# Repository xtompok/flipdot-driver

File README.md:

# flipdot-driver
Driver for flipdot displays

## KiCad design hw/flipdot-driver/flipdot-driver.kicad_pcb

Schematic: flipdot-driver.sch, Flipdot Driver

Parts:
C2: 47u; CP_Radial_D6.3mm_P2.50mm
C5, C6, C7, C8, C17, C22: 100n; C_0603_1608Metric
C9: 10u; C_0805_2012Metric
C10: 10n; C_0603_1608Metric
C11: 22u; C_0805_2012Metric
C12, C13: 10p; C_0603_1608Metric
C14, C15: 27p; C_0603_1608Metric
C16, C21, C23: 680u; CP_Radial_D10.0mm_P5.00mm
C18, C19: 470n; C_0603_1608Metric
C20: 1u; C_0603_1608Metric
D2: SK34; D_SMC
D6: SK33; D_SMC
D7, D8: LED; LED_D3.0mm
F1: 200mA; Fuse_1206_3216Metric
F2: Polyfuse; Fuse_1812_4532Metric
FID1, FID2, FID3: Fiducial; Fiducial_0.75mm_Dia_1.5mm_Outer
H1, H2: MountingHole_Pad; MountingHole_3.2mm_M3_DIN965_Pad
J1: DISPLAY; IDC-Header_2x10_P2.54mm_Vertical
J2: NRF_CON; PinSocket_2x04_P2.54mm_Vertical
J3: Prog; Molex_KK-254_AE-6410-05A_1x05_P2.54mm_Vertical
J4: I2C; Molex_KK-254_AE-6410-04A_1x04_P2.54mm_Vertical
J5: USART; Molex_KK-254_AE-6410-05A_1x05_P2.54mm_Vertical
J6: USB; Molex_KK-254_AE-6410-04A_1x04_P2.54mm_Vertical
J7: USB_B_Micro; USB_Micro-B
J8: RST; PinSocket_1x02_P2.54mm_Vertical
J9: MAIN_Power; PhoenixContact_MC-G_02x3.81mm_Angled
L2: 68u; L_12x12mm_H8mm
Q1, Q2, Q3, Q4, Q5, Q6, Q7, Q8, Q9, Q10, Q11, Q12, Q13, Q14: MMBTA64; SOT23-3
Q15, Q16, Q17, Q18: Q_NMOS_GSD; SOT-23
R3, R4, R8, R9: 330R; R_0603_1608Metric
R5, R10, R13, R16, R27, R28, R29, R30, R31, R32, R33, R34: 12k; R_0603_1608Metric
R6: 30k; R_0603_1608Metric
R7: 1.3k; R_0603_1608Metric
R11, R12, R36: 1k5; R_0603_1608Metric
R35: 1M; R_0603_1608Metric
RN1, RN2, RN3, RN4: 10k; R_Array_Convex_4x0603
RN5: 22R; R_Array_Convex_2x0402
TP1, TP2: TestPoint; TestPoint_THTPad_2.5x2.5mm_Drill1.2mm
U1: AT25xxx; SO-8_5.3x6.2mm_P1.27mm
U2, U5: ULN2003A; SOIC-16_3.9x9.9mm_P1.27mm
U3: USBLC6-2SC6; SOT-23-6
U4: AZ1117-3.3; SOT-223-3_TabPin2
U6: stm32_STM32F103C(8-B)Tx; LQFP-48_7x7mm_P0.5mm
U7, U9: 74HC595; SOIC-16_3.9x9.9mm_P1.27mm
U8: AX5201; HSOP-8-1EP_3.9x4.9mm_P1.27mm_EP2.41x3.1mm
Y1: 32768; Crystal_Round_D3.0mm_Vertical
Y2: 8MHz/20pF; Crystal_HC49-U_Vertical

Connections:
+3V3: C5.1, C6.1, C7.1, C8.1, C11.1, C22.1, J2.1, J3.4, J4.4, J5.1, Q15.1 (G), Q16.1 (G), Q17.1 (G), Q18.1 (G), R10.1, R11.1, R12.1, R13.2, R27.1, R28.1, R31.1, R32.1, R36.1, U1.3 (~WP), U1.7 (~HOLD), U1.8 (VCC), U4.2 (VO), U6.1, U6.9, U6.24, U6.36, U6.48, U7.10 (~SRCLR), U7.16 (VCC), U9.10 (~SRCLR), U9.16 (VCC)
+12V: C9.1, C16.1, C17.1, C18.1, F1.1, F2.1, L2.1, R29.1, R30.1, R33.1, R34.1, U4.3 (VI), U8.2
+24V: C2.1, C20.1, C21.1, C23.1, D2.1, Q1.2 (E), Q2.2 (E), Q3.2 (E), Q4.2 (E), Q5.2 (E), Q6.2 (E), Q7.2 (E), Q8.2 (E), Q9.2 (E), Q10.2 (E), Q11.2 (E), Q12.2 (E), Q13.2 (E), Q14.2 (E), R6.1, U2.9 (COM), U5.9 (COM)
/24V_EN: R5.1, U6.16, U8.1
/BOOT1: R10.2, TP2.1, U6.20
/FLASH_SS: U1.1 (~CS), U6.17
/I2C_SCL: J4.2, R11.2, U6.21
/I2C_SDA: J4.1, R12.2, U6.22
/LED1: D7.2, U6.11
/LED2: D8.2, U6.12
/LV_CLK: Q18.2 (S), R32.2, U6.43
/LV_DATA: Q15.2 (S), R27.2, U6.45
/LV_RET: Q16.2 (S), R28.2, U6.46
/LV_RST: Q17.2 (S), R31.2, U6.42
/NRF_CE: J2.4, U6.29
/NRF_IRQ: J2.7
/NRF_SS: J2.3, U6.25
/NRST: C10.1, J3.5, J8.2, R13.1, U6.7
/P_CLK: J1.18, Q18.3 (D), R34.2
/P_DATA: J1.15, Q15.3 (D), R29.2
/P_RET: J1.16, Q16.3 (D), R30.2
/P_RST: J1.17, Q17.3 (D), R33.2
/P_VCC: F1.2, J1.19
/ROW_1N: J1.7, Q1.3 (C)
/ROW_1P: J1.14, Q8.3 (C)
/ROW_2N: J1.6, Q2.3 (C)
/ROW_2P: J1.13, Q9.3 (C)
/ROW_3N: J1.5, Q3.3 (C)
/ROW_3P: J1.12, Q10.3 (C)
/ROW_4N: J1.4, Q4.3 (C)
/ROW_4P: J1.11, Q11.3 (C)
/ROW_5N: J1.3, Q5.3 (C)
/ROW_5P: J1.10, Q12.3 (C)
/ROW_6N: J1.2, Q6.3 (C)
/ROW_6P: J1.9, Q13.3 (C)
/ROW_7N: J1.1, Q7.3 (C)
/ROW_7P: J1.8, Q14.3 (C)
/SPI_MISO: J2.8, U1.2 (MISO), U6.27
/SPI_MOSI: J2.5, U1.5 (MOSI), U6.28
/SPI_SCK: J2.6, U1.6 (SCK), U6.26
/SR_CLK: U6.39, U7.11 (SRCLK), U9.11 (SRCLK)
/SR_DATA1: U6.41, U7.14 (SER)
/SR_DATA2: U7.9 (QH'), U9.14 (SER)
/SR_STROBE: U6.40, U7.12 (RCLK), U9.12 (RCLK)
/SWCLK: J3.2, U6.37
/SWDIO: J3.3, U6.34
/USART_RX: R3.1, U6.31
/USART_TX: R4.1, U6.30
/USB1_N: RN5.1 (R1.1), U3.3 (IO2)
/USB1_P: R36.2, RN5.2 (R2.1), U3.1 (IO1)
/USB2_N: J6.3, J7.2 (D-), U3.4 (IO2)
/USB2_P: J6.2, J7.3 (D+), U3.6 (IO1)
/USB_N: RN5.4 (R1.2), U6.32
/USB_P: RN5.3 (R2.2), U6.33
/~SR_OE: U6.38, U7.13 (~OE), U9.13 (~OE)
GND: C2.2, C5.2, C6.2, C7.2, C8.2, C9.2, C10.2, C11.2, C12.2, C13.2, C14.2, C15.2, C16.2, C17.2, C18.2, C19.2, C20.2, C21.2, C22.2, C23.2, H1.1, H2.1, J1.20, J2.2, J3.1, J4.3, J5.3, J6.1, J7.5 (GND), J7.6 (Shield), J8.1, J9.1, R5.2, R7.2, R8.2, R9.2, R16.2, U1.4 (GND), U2.8 (GND), U3.2 (GND), U4.1 (GND), U5.8 (GND), U6.8, U6.23, U6.35, U6.47, U7.8 (GND), U8.7, U8.8, U9.8 (GND)
unnamed: C12.1, U6.4, Y1.1
unnamed: C13.1, U6.3, Y1.2
unnamed: C14.1, R35.2, U6.6, Y2.1
unnamed: C15.1, R35.1, U6.5, Y2.2
unnamed: C19.1, U8.4
unnamed: D2.2, L2.2, U8.5, U8.6, U8.9
unnamed: D6.1, F2.2
unnamed: D6.2, J9.2
unnamed: D7.1, R8.1
unnamed: D8.1, R9.1
unnamed: J5.4, R4.2
unnamed: J5.5, R3.2
unnamed: J6.4, J7.1 (VBUS), U3.5 (VBUS)
unnamed: Q1.1 (B), RN1.8 (R1.2)
unnamed: Q2.1 (B), RN1.7 (R2.2)
unnamed: Q3.1 (B), RN1.6 (R3.2)
unnamed: Q4.1 (B), RN1.5 (R4.2)
unnamed: Q5.1 (B), RN2.8 (R1.2)
unnamed: Q6.1 (B), RN2.7 (R2.2)
unnamed: Q7.1 (B), RN2.6 (R3.2)
unnamed: Q8.1 (B), RN3.8 (R1.2)
unnamed: Q9.1 (B), RN3.7 (R2.2)
unnamed: Q10.1 (B), RN3.6 (R3.2)
unnamed: Q11.1 (B), RN3.5 (R4.2)
unnamed: Q12.1 (B), RN4.8 (R1.2)
unnamed: Q13.1 (B), RN4.7 (R2.2)
unnamed: Q14.1 (B), RN4.6 (R3.2)
unnamed: R6.2, R7.1, U8.3
unnamed: R16.1, TP1.1, U6.44
unnamed: RN1.1 (R1.1), U2.16 (O1)
unnamed: RN1.2 (R2.1), U2.15 (O2)
unnamed: RN1.3 (R3.1), U2.14 (O3)
unnamed: RN1.4 (R4.1), U2.13 (O4)
unnamed: RN2.1 (R1.1), U2.12 (O5)
unnamed: RN2.2 (R2.1), U2.11 (O6)
unnamed: RN2.3 (R3.1), U2.10 (O7)
unnamed: RN3.1 (R1.1), U5.16 (O1)
unnamed: RN3.2 (R2.1), U5.15 (O2)
unnamed: RN3.3 (R3.1), U5.14 (O3)
unnamed: RN3.4 (R4.1), U5.13 (O4)
unnamed: RN4.1 (R1.1), U5.12 (O5)
unnamed: RN4.2 (R2.1), U5.11 (O6)
unnamed: RN4.3 (R3.1), U5.10 (O7)
unnamed: U2.1 (I1), U7.7 (QH)
unnamed: U2.2 (I2), U7.6 (QG)
unnamed: U2.3 (I3), U7.5 (QF)
unnamed: U2.4 (I4), U7.4 (QE)
unnamed: U2.5 (I5), U7.3 (QD)
unnamed: U2.6 (I6), U7.2 (QC)
unnamed: U2.7 (I7), U7.1 (QB)
unnamed: U5.1 (I1), U9.7 (QH)
unnamed: U5.2 (I2), U9.6 (QG)
unnamed: U5.3 (I3), U9.5 (QF)
unnamed: U5.4 (I4), U9.4 (QE)
unnamed: U5.5 (I5), U9.3 (QD)
unnamed: U5.6 (I6), U9.2 (QC)
unnamed: U5.7 (I7), U9.1 (QB)

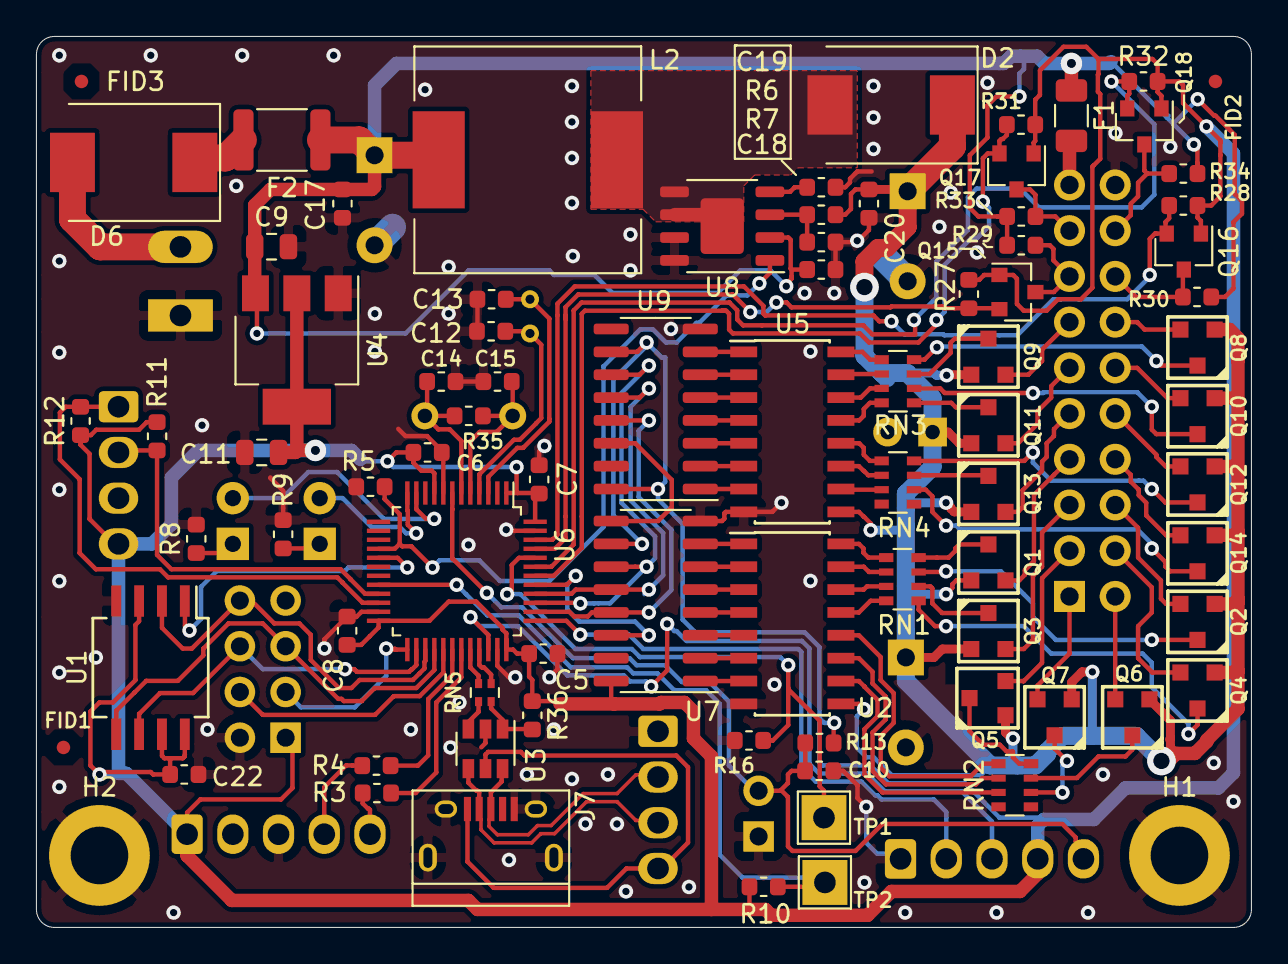
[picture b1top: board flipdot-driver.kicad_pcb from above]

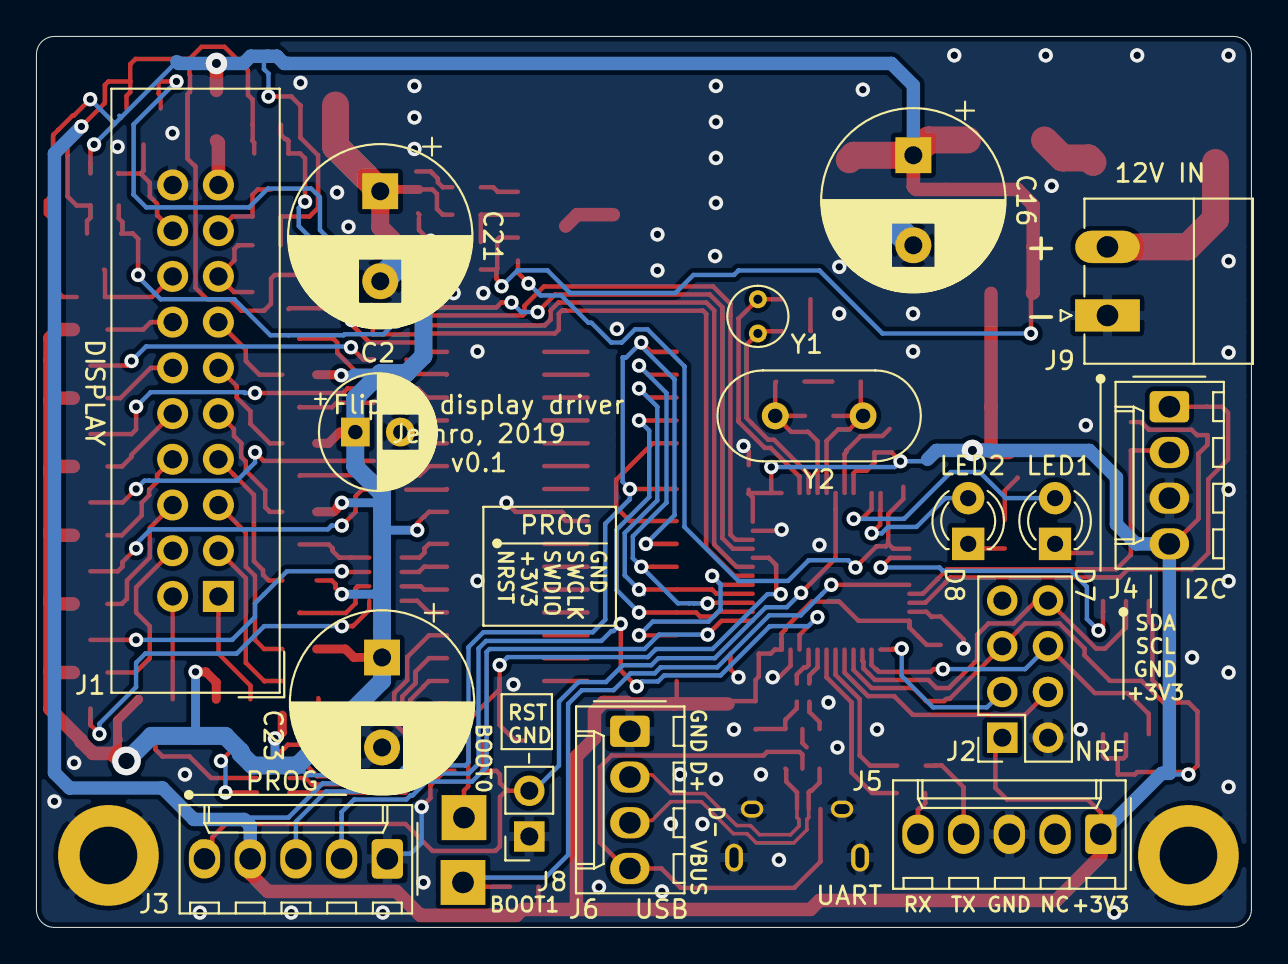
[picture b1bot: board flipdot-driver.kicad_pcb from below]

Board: 2 copper layers, 67.5 x 49.5 mm, 99 parts (16 on the bottom side), 112 nets.

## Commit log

2018-12-26 Added schematic stub.
2019-05-31 Last version before 74HC595.
    Only partially routed.
2019-05-31 Added symbol lib.
2019-05-31 Added 74HC595 and AX5201
2019-06-01 Routed, with unused parts.
2019-06-01 Routed, without unused parts.
2019-06-01 Placed labels, NRF connector mirrored.
2019-06-01 Forgotten labes.
2019-06-01 Ready for manufacturing.
2019-06-01 Better ground planes.
2019-07-27 First software (only LED and USART test).
2019-07-29 First tested and working version.
2019-07-29 Ability to display characters, untested.
2019-07-30 Somehow working, not deterministic.
2019-08-03 First working SW.
2019-08-16 Simple clock.
2019-08-17 Countdown and timer.
